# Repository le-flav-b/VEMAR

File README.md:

Technical Documentation: Project VEMAR
======================================
Vehicle for Exploration, Mapping & Air-quality Reconnaissance
-------------------------------------------------------------

**VEMAR** is a modular platform designed for environmetal monitoring and spatial mapping.
By combining real-time locomotion control with a verstile *plug-and-play* sensor architecture, VEMAR provides a comprehensive solution for atmospheric analysis in diverse environments.

## System Overview

The VEMAR system consists of three primary layers:
* A remote controlled vehicle
* Modular Sensors
* Remote Controller

The architecture is designed for high adaptability, allowing users to reconfigure the hardware loadout without complex software recalibration.

### Mobile Platform
* Locomotion: Multi-directional drive system.
* Storage: Integrated SD card slot for localized data logging (JSON format)
* Connectivity: Real-time telemetry link between the vehicle and the handheld controller.

### Modular Sensor Suite
The system utilizes a unified interface that allows the controller to automatically detect and initialize snensors upon connection.

| Sensor ID | Sensor Category | Parameters Measured                                         |
|:---------:|:---------------:|:-----------------------------------------------------------:|
| 1         | Atmospheric     | Temperature, Humidity, Barometric Pressure, PM2.5, PM10     |
| 2         | Gas Analysis    | O2, CO2, CO, NH3, NO2                                       |
| 3         | Mapping         | LiDAR (Light Detection and Ranging) for 2D spatial modeling |
| 4         | Radiation       | Ionizing radiation levels (Geiger-Müller detection)         |

## Functional Capabilities

### Remote Control

The end-user manages the vehicle's navigation via a dedicated controller.
The control link facilites:
* Manual Drive: Real-time steering.
* Data Visualization: A live feedback loop where sensor readings are streamed directly to the controller's display.

### Plug-and-Play Architecture

VEMAR eliminates the need for manual firmware updates when switching hardware.
* Auto-Detection: When a sensor module is attached, the controller identifies the hardware ID and adjusts the UI to display the relevant metrics.
* Hot-Swapping: Sensors can be exchanged in the field to pivot from air-quality monitoring to radiation detection or mapping.

### Data Management

The system supports dual-stream data handling:
* Live Monitoring: Immediate visaul feedback on the controller screen for rapid assessment.
* Archival Recording: On-demand recording to an onboard **SD Card**. this ensures high-fidelity data retention for post-mission analysis and mapping reconstruction.

> Caution: Removing the SD card before stopping the recording may result data corruption of the sd card.
It is recommended to wait at least 5 seconds after disabling saving before safely removing the SD card.

## Operation Workflow

1. Initialization: Power on the vehicle and controller.
2. Module Integration: Plug in desired sensor modules.
3. Verification: Cycle through sensor module readings by pressing the 'A' button on the controller.
4. Deployment: Navigate VEMAR into the target zone while monitoring live data.
5. Logging: Toggle the `Record` function to save data to the SD card by pressing 'B'.
6. Recovery: Disable data logging and retrieve the SD card for data processing.

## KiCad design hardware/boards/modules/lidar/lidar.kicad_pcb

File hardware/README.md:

explain the folder + show what can be found where

NEED TO CLEAN UP LIBS, some are not used, and architecture is strange
check component one by one and make agreement (e.g : there is 4pin_quartz in differents libs and the symbol don't even look the same)

and also COMPLETE SYMBOLS with datasheet, footprint, ...

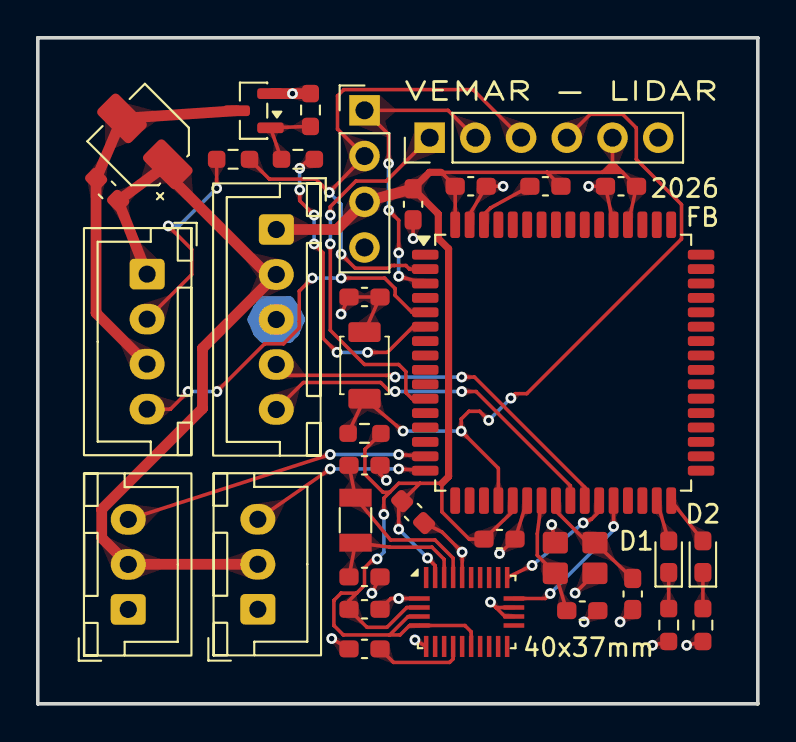
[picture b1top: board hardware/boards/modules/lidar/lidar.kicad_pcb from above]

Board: 2 copper layers, 40.0 x 37.0 mm, 35 parts (0 on the bottom side), 28 nets.

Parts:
C1, C5, C6, C7, C8, C10, C13, C14: 100nF; C_0603_1608Metric_Pad1.08x0.95mm_HandSolder
C2, C3, C11, C12: 12pF; C_0603_1608Metric_Pad1.08x0.95mm_HandSolder
C4: 4.7uF; C_0603_1608Metric_Pad1.08x0.95mm_HandSolder
C9: 10uF; CP_Elec_4x5.4
C15: 1uF; C_0603_1608Metric_Pad1.08x0.95mm_HandSolder
D1: GREEN; LED_0603_1608Metric_Pad1.05x0.95mm_HandSolder
D2: RED; LED_0603_1608Metric_Pad1.05x0.95mm_HandSolder
J1: JST; JST_XH_B5B-XH-A_1x05_P2.50mm_Vertical
J2: Dupont; PinHeader_1x06_P2.54mm_Vertical
J3: Dupont; PinHeader_1x04_P2.54mm_Vertical
J4: JST; JST_XH_B4B-XH-A_1x04_P2.50mm_Vertical
J5, J6: JST; JST_XH_B3B-XH-A_1x03_P2.50mm_Vertical
Q1: AO3400A; SOT-23
R1, R5: 10K; R_0603_1608Metric_Pad0.98x0.95mm_HandSolder
R2, R3: 330; R_0603_1608Metric_Pad0.98x0.95mm_HandSolder
R4: 100; R_0603_1608Metric_Pad0.98x0.95mm_HandSolder
R6: 1K; R_0603_1608Metric_Pad0.98x0.95mm_HandSolder
SW1: SW_Push; SW_Tactile3x2.5
U1: ATmega128A; TQFP-64_14x14mm_P0.8mm
U2: BNO055; BNO055_Hand_Soldering_LGA-28_5.2x3.8mm_P0.5mm
Y1: 16MHz; crys_osc_smd3225_4
Y2: 32.768kHz; Crystal_SMD_3215-2Pin_3.2x1.5mm

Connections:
3V3: C4.1, C5.1, C6.1, C7.1, C8.1, C13.2, C14.1, J1.1 (3V3), J2.5, J3.3, R1.1, U1.21 (VCC), U1.52 (VCC), U1.64 (AVCC), U2.3 (VDD), U2.4 (~BOOT_LOAD_PIN), U2.5 (PS1), U2.11 (~RESET), U2.28 (VDDIO)
5V: C9.1, C10.1, J1.2 (5V), J4.1, J5.2, J6.2
D1: D1.2 (A), U1.31 (PD6)
D2: D2.2 (A), U1.32 (PD7)
GND: C1.1, C1.2, C2.2, C3.2, C4.2, C5.2, C6.2, C7.2, C11.2, C12.2, C13.1, C14.2, C15.2, J1.3 (GND), J2.6, J3.4, J5.1, J6.1, Q1.2 (S), R2.2, R3.2, R5.1, SW1.1, U1.22 (GND), U1.53 (GND), U1.63 (GND), U2.2 (GND), U2.6 (PS0), U2.17 (COM3), U2.18 (COM2), U2.25 (GNDIO), Y1.2 (G), Y1.4 (G)
LIDAR_EN: R4.1, U1.6 (PE4)
LIDAR_PWM: J4.4, U1.5 (PE3)
unnamed: D1.1 (K), R2.1
unnamed: D2.1 (K), R3.1
unnamed: J4.2, R6.2
unnamed: C9.2, C10.2, J4.3, Q1.3 (D)
unnamed: Q1.1 (G), R4.2, R5.2
unnamed: C8.2, U1.62 (AREF)
unnamed: C2.1, U1.24 (XTAL1), Y1.1
unnamed: C3.1, U1.23 (XTAL2), Y1.3
unnamed: C15.1, U2.9 (CAP)
unnamed: C12.1, U2.27 (XIN32), Y2.1
unnamed: C11.1, U2.26 (XOUT32), Y2.2
RST: J2.4, R1.2, SW1.2, U1.20 (~RESET)
RX0: J2.3, J3.2, R6.1, U1.2 (PE0)
RX1: U1.27 (PD2), U2.20 (COM0)
SCK: J2.1, U1.11 (PB1)
SCL: J1.5 (SCL), U1.25 (PD0)
SDA: J1.4 (SDA), U1.26 (PD1)
SERVO_A_PWM: J5.3, U1.15 (PB5)
SERVO_B_PWM: J6.3, U1.16 (PB6)
TX0: J2.2, J3.1, U1.3 (PE1)
TX1: U1.28 (PD3), U2.19 (COM1)

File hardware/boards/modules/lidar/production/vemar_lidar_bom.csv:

Designator,Footprint,Quantity,Value,LCSC Part #
"C1, C10, C13, C14, C5, C6, C7, C8",0603,8,100nF,
"C11, C12, C2, C3",0603,4,12pF,
C15,0603,1,1uF,
C4,0603,1,4.7uF,
C9,CP_Elec_4x5.4,1,10uF,
D1,0603,1,GREEN,
D2,0603,1,RED,
J1,JST_XH_B5B-XH-A_1x05_P2.50mm_Vertical,1,JST,
J2,PinHeader_1x06_P2.54mm_Vertical,1,Dupont,
J3,PinHeader_1x04_P2.54mm_Vertical,1,Dupont,
J4,JST_XH_B4B-XH-A_1x04_P2.50mm_Vertical,1,JST,
"J5, J6",JST_XH_B3B-XH-A_1x03_P2.50mm_Vertical,2,JST,
Q1,SOT-23,1,AO3400A,
"R1, R5",0603,2,10K,
"R2, R3",0603,2,330,
R4,0603,1,100,
R6,0603,1,1K,
SW1,SW_Tactile3x2.5,1,SW_Push,
U1,TQFP-64_14x14mm_P0.8mm,1,ATmega128A,
U2,BNO055_Hand_Soldering_LGA-28_5.2x3.8mm_P0.5mm,1,BNO055,
Y1,crys_osc_smd3225_4,1,16MHz,
Y2,Crystal_SMD_3215-2Pin_3.2x1.5mm,1,32.768kHz,

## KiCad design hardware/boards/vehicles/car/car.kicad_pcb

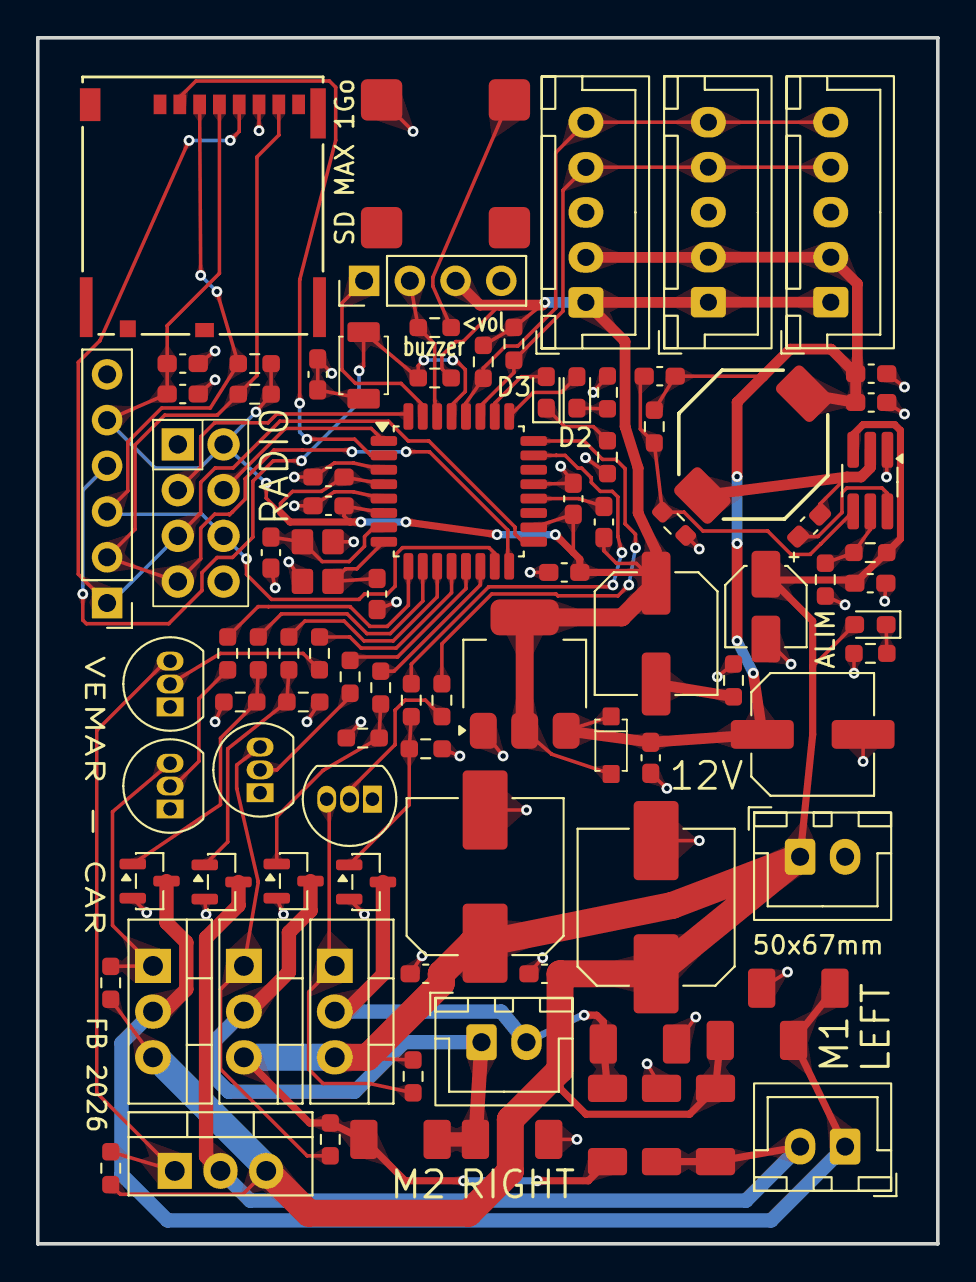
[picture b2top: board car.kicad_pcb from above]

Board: 2 copper layers, 50.0 x 67.0 mm, 94 parts (0 on the bottom side), 53 nets.

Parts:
BT1: JST; JST_XH_B2B-XH-A_1x02_P2.50mm_Vertical
BZ1: Buzzer; buzzer_8.5x8.5
C1, C5, C6, C7, C8, C10, C11, C16, C18, C21, C23: 100nF; C_0603_1608Metric_Pad1.08x0.95mm_HandSolder
C2, C3: 12pF; C_0603_1608Metric_Pad1.08x0.95mm_HandSolder
C4: 4.7uF; C_0603_1608Metric_Pad1.08x0.95mm_HandSolder
C9: 10uF; CP_Elec_4x5.4
C12, C13: 22uF; C_0603_1608Metric_Pad1.08x0.95mm_HandSolder
C14: 75pF; C_0603_1608Metric_Pad1.08x0.95mm_HandSolder
C15, C17: 22uF; CP_Elec_6.3x5.4
C19: 10uF; C_0603_1608Metric_Pad1.08x0.95mm_HandSolder
C20, C22: 470uF; CP_Elec_8x10.5
D1, D3: RED; LED_0603_1608Metric_Pad1.05x0.95mm_HandSolder
D2: GREEN; LED_0603_1608Metric_Pad1.05x0.95mm_HandSolder
D4: RS1MFA; D_SOD123
D5, D6, D7, D8, D9, D10, D11, D12: SS36; SMA(DO-214AC)
J1: Dupont; PinHeader_1x06_P2.54mm_Vertical
J2: Dupont; PinHeader_1x04_P2.54mm_Vertical
J3: Dupont; Pin_02x04
J4, J5, J6: JST; JST_XH_B5B-XH-A_1x05_P2.50mm_Vertical
L1: 10uH; Inductor_octogone
M1: LEFT; JST_XH_B2B-XH-A_1x02_P2.50mm_Vertical
M2: RIGHT; JST_XH_B2B-XH-A_1x02_P2.50mm_Vertical
Q1, Q2, Q7, Q8: FQP27P06; TO-220-3_Vertical
Q3, Q4, Q9, Q10: AO3400A; SOT-23
Q5, Q6, Q11, Q12: 2N3904; TO-92_Inline
R1: 680; R_0603_1608Metric_Pad0.98x0.95mm_HandSolder
R2, R13, R14, R21, R22, R29, R30: 10K; R_0603_1608Metric_Pad0.98x0.95mm_HandSolder
R3, R4: 330; R_0603_1608Metric_Pad0.98x0.95mm_HandSolder
R5: ?; R_0603_1608Metric_Pad0.98x0.95mm_HandSolder
R6, R7, R19, R20, R27, R28: 4.7K; R_0603_1608Metric_Pad0.98x0.95mm_HandSolder
R8: 511K; R_0603_1608Metric_Pad0.98x0.95mm_HandSolder
R9: 105K; R_0603_1608Metric_Pad0.98x0.95mm_HandSolder
R10: 43.2K; R_0603_1608Metric_Pad0.98x0.95mm_HandSolder
R11: 5.76K; R_0603_1608Metric_Pad0.98x0.95mm_HandSolder
R12: 1; R_0603_1608Metric_Pad0.98x0.95mm_HandSolder
R15, R16, R23, R24: 1K; R_0603_1608Metric_Pad0.98x0.95mm_HandSolder
R17, R18, R25, R26: 47; R_0603_1608Metric_Pad0.98x0.95mm_HandSolder
SD1: SD Card Slot; SD_SLOT
SW1: SW_Push; SW_Tactile3x2.5
U1: ATmega328P-A; TQFP-32_7x7mm_P0.8mm
U2: TPS54302; TSOT-23-6_HandSoldering
U3: AMS1117-3.3; SOT-223-3_TabPin2
Y1: 16MHz; crys_osc_smd3225_4

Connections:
3V3: C4.1, C5.1, C6.1, C7.1, C8.1, C17.1, C18.1, C19.1, D4.2 (A), J1.5, J2.3, J3.8, J4.1, J5.1, J6.1, R2.1, R6.1, R7.1, R13.1, R14.1, SD1.4 (VDD), U1.4 (VCC), U1.6 (VCC), U1.18 (AVCC), U3.2 (VO)
5V: C12.1, C13.2, C14.2, C15.1, C16.2, D4.1 (K), J4.2, J5.2, J6.2, L1.2, R10.2, U3.3 (VI)
12V: BT1.1 (+), C9.1, C10.2, C20.1, C21.1, C22.1, C23.1, D1.2 (A), D5.1 (K), D7.1 (K), D9.1 (K), D11.1 (K), Q1.3 (S), Q2.3 (S), Q7.3 (S), Q8.3 (S), R8.2, R19.2, R20.1, R27.2, R28.1, U2.3 (VIN)
D2: D2.2 (A), U1.25 (PC2)
D3: D3.2 (A), U1.26 (PC3)
GND: BT1.2 (-), BZ1.2, C1.1, C1.2, C2.2, C3.2, C4.2, C5.2, C6.2, C7.2, C9.2, C10.1, C12.2, C13.1, C15.2, C16.1, C18.2, C19.2, C20.2, C21.2, C22.2, C23.2, D6.2 (A), D8.2 (A), D10.2 (A), D12.2 (A), J1.6, J2.4, J3.1, J4.3, J5.3, J6.3, Q3.2 (S), Q4.2 (S), Q5.1 (E), Q6.1 (E), Q9.2 (S), Q10.2 (S), Q11.1 (E), Q12.1 (E), R1.2, R3.2, R4.2, R9.1, R11.1, R12.1, R21.2, R22.1, R29.2, R30.1, SD1.6 (VSS), SW1.1, U1.3 (GND), U1.5 (GND), U1.21 (GND), U2.1 (GND), U3.1 (GND), Y1.2 (G), Y1.4 (G)
M1_EN_CCW: R16.1, U1.12 (PB0)
M1_EN_CW: R18.2, U1.11 (PD7)
M1_PWM_CCW: R17.2, U1.10 (PD6)
M1_PWM_CW: R15.1, U1.9 (PD5)
M2_EN_CCW: R24.1, U1.24 (PC1)
M2_EN_CW: R26.2, U1.23 (PC0)
M2_PWM_CCW: R25.2, U1.14 (PB2)
M2_PWM_CW: R23.1, U1.13 (PB1)
MISO: J1.2, J3.4, R14.2, SD1.7 (DAT0), U1.16 (PB4)
MOSI: J1.3, J3.6, R13.2, SD1.3 (CMD), U1.15 (PB3)
unnamed: BZ1.1, R5.2
unnamed: C17.2, R12.2
unnamed: D1.1 (K), R1.1
unnamed: D2.1 (K), R3.1
unnamed: D3.1 (K), R4.1
unnamed: D5.2 (A), D6.1 (K), M1.1 (+), Q1.2 (D), Q3.3 (D)
unnamed: D7.2 (A), D8.1 (K), M1.2 (-), Q2.2 (D), Q4.3 (D)
unnamed: D9.2 (A), D10.1 (K), M2.1 (+), Q7.2 (D), Q9.3 (D)
unnamed: D11.2 (A), D12.1 (K), M2.2 (-), Q8.2 (D), Q10.3 (D)
unnamed: Q1.1 (G), Q5.3 (C), R19.1
unnamed: Q2.1 (G), Q6.3 (C), R20.2
unnamed: Q3.1 (G), R17.1, R21.1
unnamed: Q4.1 (G), R18.1, R22.2
unnamed: Q5.2 (B), R15.2
unnamed: Q6.2 (B), R16.2
unnamed: Q9.1 (G), R25.1, R29.1
unnamed: Q10.1 (G), R26.1, R30.2
unnamed: Q11.2 (B), R23.2
unnamed: Q7.1 (G), Q11.3 (C), R27.1
unnamed: Q12.2 (B), R24.2
unnamed: Q8.1 (G), Q12.3 (C), R28.2
unnamed: C8.2, U1.20 (AREF)
unnamed: C2.1, U1.7 (XTAL1/PB6), Y1.1
unnamed: C3.1, U1.8 (XTAL2/PB7), Y1.3
unnamed: C11.1, U2.6 (BOOT)
unnamed: R8.1, R9.2, U2.5 (EN)
unnamed: C14.1, R10.1, R11.2, U2.4 (FB)
unnamed: C11.2, L1.1, U2.2 (SW)
RC_CS: J3.7, U1.1 (PD3)
RC_EN: J3.2, U1.32 (PD2)
RST: J1.4, R2.2, SW1.2, U1.29 (~RESET/PC6)
RX: J2.2, R5.1, U1.30 (PD0)
SCK: J1.1, J3.3, SD1.5 (CLK), U1.17 (PB5)
SCL: J4.5, J5.5, J6.5, R7.2, U1.28 (PC5)
SDA: J4.4, J5.4, J6.4, R6.2, U1.27 (PC4)
SD_CS: SD1.2 (CD/DAT3), U1.2 (PD4)
TX: J2.1, U1.31 (PD1)

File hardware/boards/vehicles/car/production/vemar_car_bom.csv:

Designator,Footprint,Quantity,Value,LCSC Part #
BT1,JST_XH_B2B-XH-A_1x02_P2.50mm_Vertical,1,JST,
BZ1,buzzer_8.5x8.5,1,Buzzer,
"C1, C10, C11, C16, C18, C21, C23, C5, C6, C7, C8",0603,11,100nF,
"C12, C13",0603,2,22uF,
C14,0603,1,75pF,
"C15, C17",CP_Elec_6.3x5.4,2,22uF,
C19,0603,1,10uF,
"C2, C3",0603,2,12pF,
"C20, C22",CP_Elec_8x10.5,2,470uF,
C4,0603,1,4.7uF,
C9,CP_Elec_4x5.4,1,10uF,
"D1, D3",0603,2,RED,
"D10, D11, D12, D5, D6, D7, D8, D9",SMA(DO-214AC),8,SS36,
D2,0603,1,GREEN,
D4,D_SOD123,1,RS1MFA,
J1,PinHeader_1x06_P2.54mm_Vertical,1,Dupont,
J2,PinHeader_1x04_P2.54mm_Vertical,1,Dupont,
J3,Pin_02x04,1,Dupont,
"J4, J5, J6",JST_XH_B5B-XH-A_1x05_P2.50mm_Vertical,3,JST,
L1,Inductor_octogone,1,10uH,
M1,JST_XH_B2B-XH-A_1x02_P2.50mm_Vertical,1,LEFT,
M2,JST_XH_B2B-XH-A_1x02_P2.50mm_Vertical,1,RIGHT,
"Q1, Q2, Q7, Q8",TO-220-3_Vertical,4,FQP27P06,
"Q10, Q3, Q4, Q9",SOT-23,4,AO3400A,
"Q11, Q12, Q5, Q6",TO-92_Inline,4,2N3904,
R1,0603,1,680,
R10,0603,1,43.2K,
R11,0603,1,5.76K,
R12,0603,1,1,
"R13, R14, R2, R21, R22, R29, R30",0603,7,10K,
"R15, R16, R23, R24",0603,4,1K,
"R17, R18, R25, R26",0603,4,47,
"R19, R20, R27, R28, R6, R7",0603,6,4.7K,
"R3, R4",0603,2,330,
R5,0603,1,?,
R8,0603,1,511K,
R9,0603,1,105K,
SD1,SD_SLOT,1,SD Card Slot,
SW1,SW_Tactile3x2.5,1,SW_Push,
U1,TQFP-32_7x7mm_P0.8mm,1,ATmega328P-A,
U2,TSOT-23-6_HandSoldering,1,TPS54302,
U3,SOT-223-3_TabPin2,1,AMS1117-3.3,
Y1,crys_osc_smd3225_4,1,16MHz,

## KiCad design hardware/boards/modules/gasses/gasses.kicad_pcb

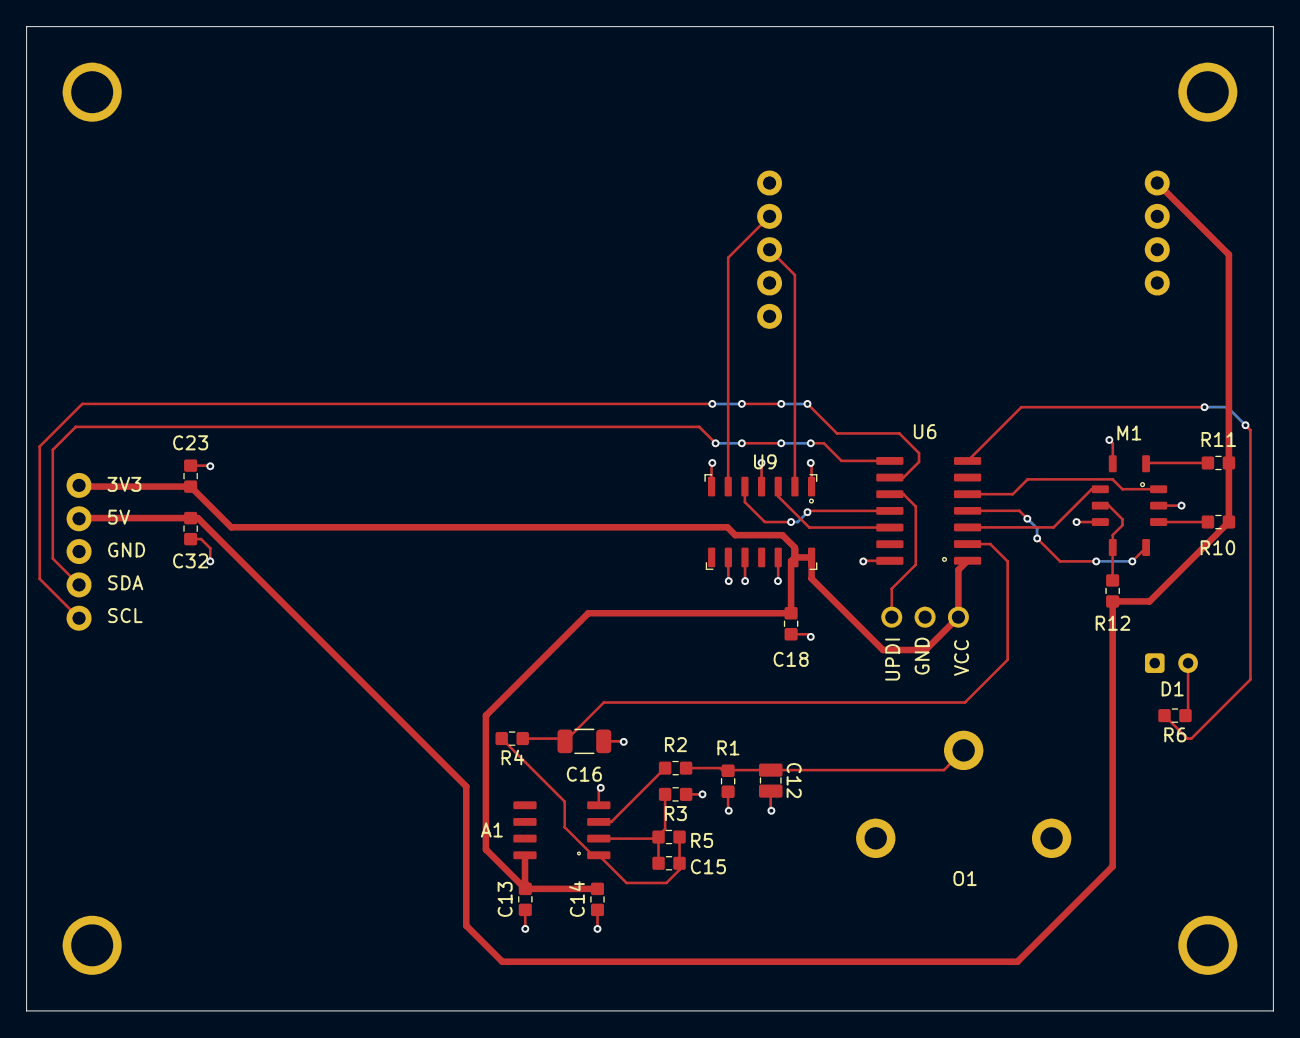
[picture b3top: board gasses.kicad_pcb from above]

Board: 2 copper layers, 95.0 x 75.0 mm, 26 parts (0 on the bottom side), 23 nets.

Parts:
A1: AD8552
C12: 4.7uF; C_0805
C13, C14, C15: 10nF; C_0603
C16: 10uF; C_1206
C18, C23, C32: 100nF; C_0603
D1: LED_3mm_THT
G2: Module Connector; GPIO_HEADER
J1: Program Header; ATtiny_Programming_Header
M1: MiCS-6814
O1: AO-03; AO_03
R1, R4: 100R; R_0603
R2, R3: 10K; R_0603
R5: 400K; R_0603
R6: 220; R_0603
R10: 27R; R_0603
R11: 130; R_0603
R12: 820R; R_0603
S5: MH-Z1911A
U6: ATtiny1614
U9: Buffer; SN74LVC125

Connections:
02_A: C16.2, R4.1, U6.2 (PA4)
3V3: A1.8 (+Vs), C13.2, C14.2, C18.1, C23.2, G2.1 (3V3), J1.1 (VCC), U6.1 (VDD), U9.13 (4OE), U9.14 (VCC)
5V: C32.1, G2.2 (5V), R10.2, R11.2, R12.1, S5.9 (VIN)
AT_GAS_RX: U6.12 (PA2), U9.3 (1Y)
AT_GAS_TX: U6.11 (PA1), U9.5 (2A)
CO2_RX: S5.4 (RX), U9.6 (2Y)
CO2_TX: S5.3 (TX), U9.2 (1A)
CO_VAL: M1.8 (H), U6.3 (PA5)
GND: A1.4 (-Vs), C12.2, C13.1, C14.1, C16.1, C18.2, C23.1, C32.2, D1.1 (K), G2.3 (GND), J1.2 (GND), M1.2 (B), M1.6 (F), M1.9 (J), O1.2 (Vsensor-), R1.1, R3.1, S5.8 (GND), U6.14 (GND), U9.1 (1OE), U9.4 (2OE), U9.7 (GND), U9.9 (3A), U9.10 (3OE), U9.12 (4A)
NH3_VAL: M1.4 (D), U6.4 (PA6)
NO2_VAL: M1.1 (A), U6.5 (PA7)
unnamed: A1.3 (+IN_A), R2.2
unnamed: A1.2 (-IN_A), C15.2, R3.2, R5.2
unnamed: A1.1 (OUT_A), C15.1, R4.2, R5.1
unnamed: D1.2 (A), R6.2
unnamed: M1.3 (C), R10.1
unnamed: M1.5 (E), M1.7 (G), R12.2
unnamed: M1.10 (K), R11.1
unnamed: C12.1, O1.1 (Vsensor+), R1.2, R2.1
SCL: G2.5 (SCL), U6.9 (PB0)
SDA: G2.4 (SDA), U6.8 (PB1)
STATUS_LED: R6.1, U6.7 (TOSC2/PB2)
UPDI: J1.3 (UPDI), U6.10 (PA0/RST/UPDI)

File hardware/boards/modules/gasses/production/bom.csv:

Designator,Footprint,Quantity,Value,LCSC Part #
"_4, _2",,2,,
"_3, ",mounting_hole,2,mounting_hole,
A1,AD8552,1,AD8552,
C12,C_0805,1,4.7uF,
"C13, C14, C15",C_0603,3,10nF,
C16,C_1206,1,10uF,
"C18, C23, C32",C_0603,3,100nF,
D1,LED_3mm_THT,1,~,
G2,GPIO_HEADER,1,Module Connector,
J1,ATtiny_Programming_Header,1,Program Header,
M1,MiCS-6814,1,MiCS-6814,
O1,AO_03,1,AO-03,
"R1, R4",R_0603,2,100R,
R10,R_0603,1,27R,
R11,R_0603,1,130,
R12,R_0603,1,820R,
"R2, R3",R_0603,2,10K,
R5,R_0603,1,400K,
R6,R_0603,1,220,
S5,MH-Z1911A,1,MH-Z1911A,
U6,ATtiny1614,1,~,
U9,SN74LVC125,1,Buffer,

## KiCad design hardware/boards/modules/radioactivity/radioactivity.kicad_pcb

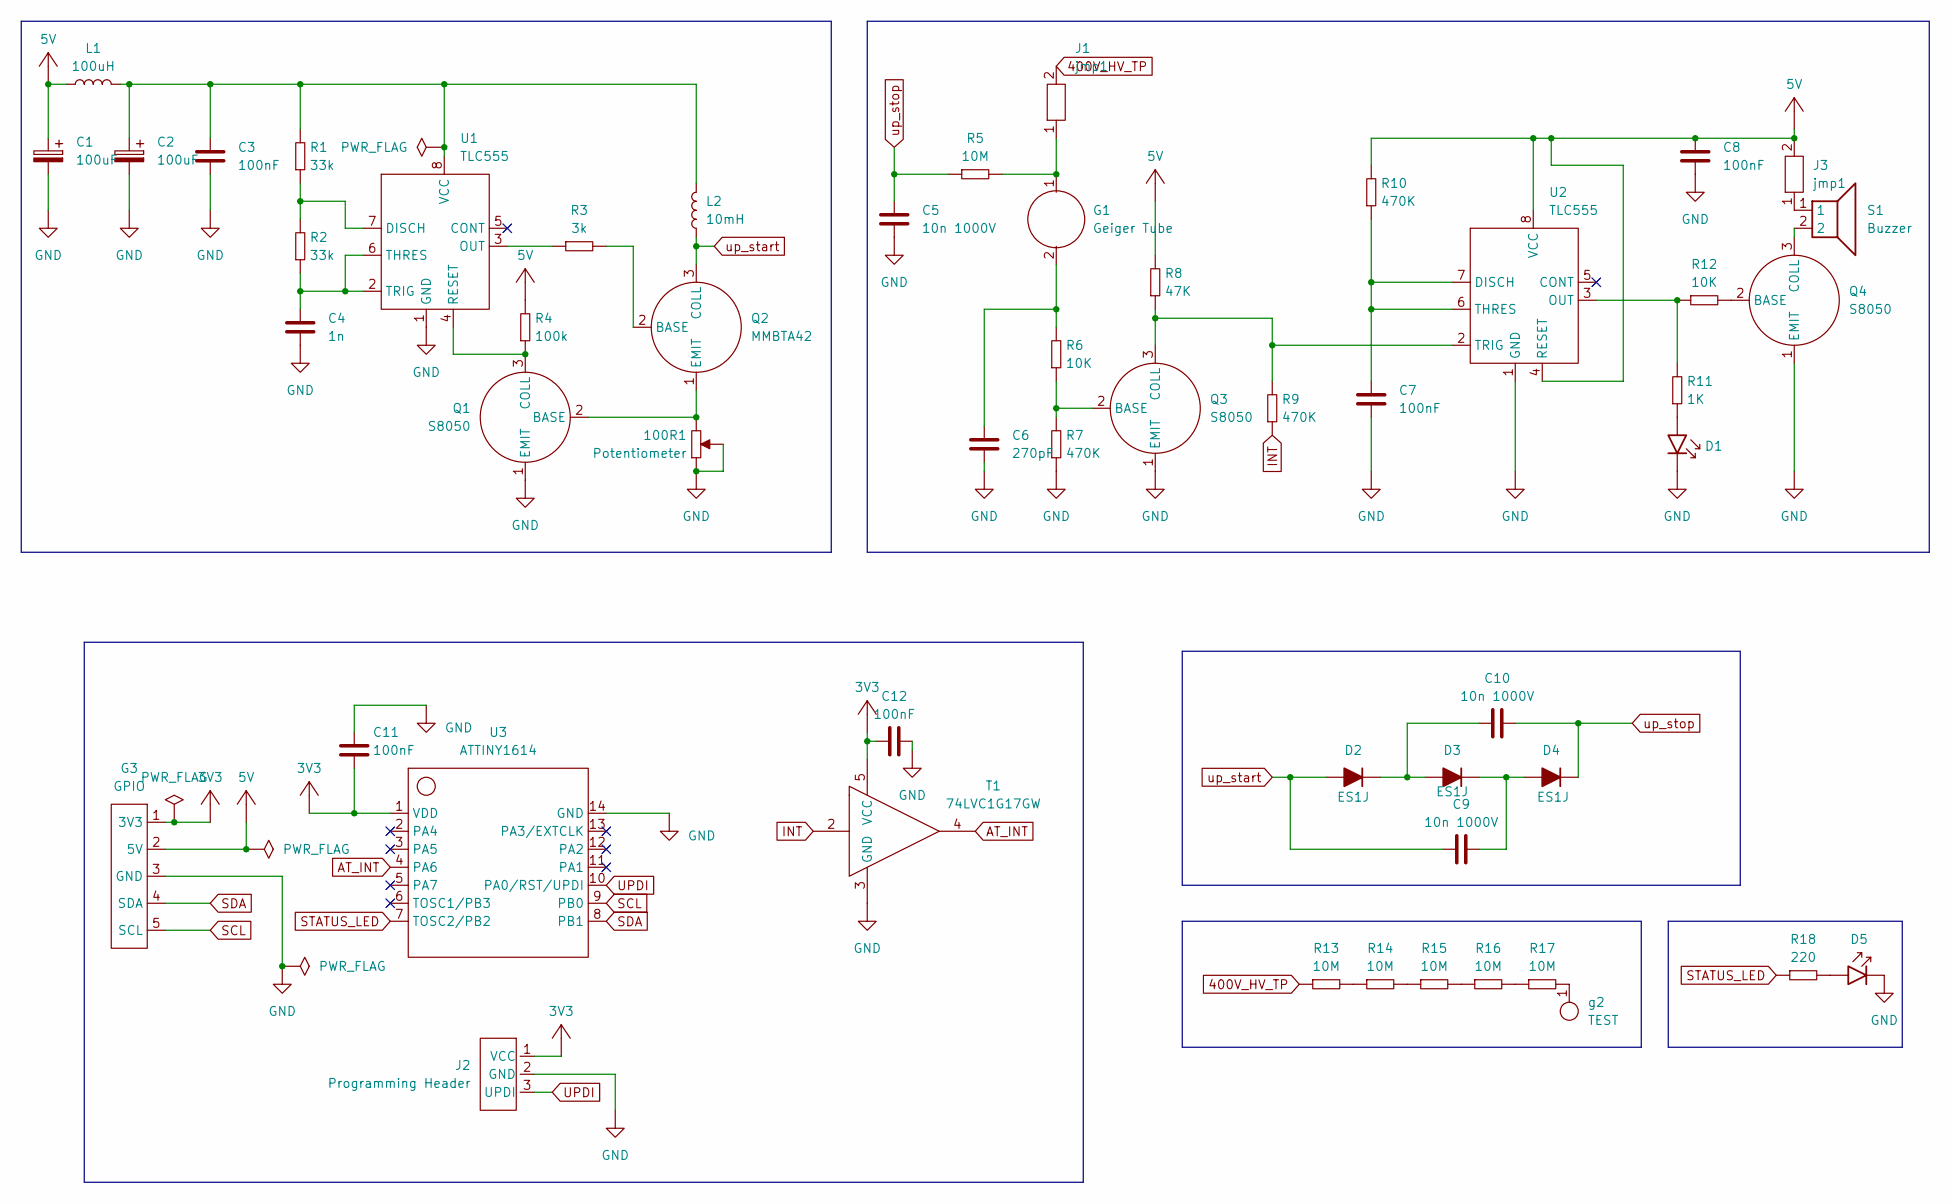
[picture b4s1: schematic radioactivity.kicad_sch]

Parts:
100R1: Potentiometer; SMD_3P_3.8X3.6
C1, C2: 100uF; C_Elec_SMD_5x5.4
C3, C7, C8, C11, C12: 100nF; C_0603
C4: 1n; C_0603
C5, C9, C10: 10n 1000V; C_1206
C6: 270pF; C_0603
D1: LED_0603
D2, D3, D4: ES1J; SMA(DO-214AC)
D5: LED_3mm_THT
G1: Geiger Tube; Geiger_Tube_J305
G3: GPIO; GPIO_HEADER
J1, J3: jmp1; Jumper_2
J2: Programming Header; ATtiny_Programming_Header
L1: 100uH; SMD(7.1x6.6)
L2: 10mH; C_0603
Q1, Q3, Q4: S8050; SOT-23
Q2: MMBTA42; SOT-23
R1, R2: 33k; R_0603
R3: 3k; R_0603
R4: 100k; R_0603
R5, R13, R14, R15, R16, R17: 10M; R_0603
R6, R12: 10K; R_0603
R7, R9, R10: 470K; R_0603
R8: 47K; R_0603
R11: 1K; R_0603
R18: 220; R_0603
S1: Buzzer; buzzer_8.5x8.5
T1: 74LVC1G17GW; SOT353
U1, U2: TLC555; SOIC-8
U3: ATTINY1614; ATtiny1614
g2: TEST; gpio_1

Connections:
400V_HV_TP: J1.2, R13.1
AT_INT: T1.4, U3.4 (PA6)
INT: R9.1, T1.2
unnamed: C6.2, G1.2, R6.2
unnamed: D1.2 (A), R11.1
unnamed: C10.1, D2.1 (K), D3.2 (A)
unnamed: C9.2, D3.1 (K), D4.2 (A)
unnamed: D5.2 (A), R18.2
unnamed: G1.1, J1.1, R5.2
unnamed: J3.1, S1.1
unnamed: 100R1.3, Q1.2 (BASE), Q2.1 (EMIT)
unnamed: Q1.3 (COLL), R4.1, U1.4 (RESET)
unnamed: Q2.2 (BASE), R3.2
unnamed: Q3.2 (BASE), R6.1, R7.2
unnamed: Q3.3 (COLL), R8.1, R9.2, U2.2 (TRIG)
unnamed: Q4.2 (BASE), R12.2
unnamed: Q4.3 (COLL), S1.2
unnamed: R13.2, R14.1
unnamed: R14.2, R15.1
unnamed: R15.2, R16.1
unnamed: R16.2, R17.1
unnamed: R17.2, g2.1
unnamed: R1.1, R2.2, U1.7 (DISCH)
unnamed: R3.1, U1.3 (OUT)
unnamed: C4.2, R2.1, U1.2 (TRIG), U1.6 (THRES)
unnamed: C7.2, R10.1, U2.6 (THRES), U2.7 (DISCH)
unnamed: R11.2, R12.1, U2.3 (OUT)
SCL: G3.5 (SCL), U3.9 (PB0)
SDA: G3.4 (SDA), U3.8 (PB1)
STATUS_LED: R18.1, U3.7 (TOSC2/PB2)
UPDI: J2.3 (UPDI), U3.10 (PA0/RST/UPDI)
up_start: C9.1, D2.2 (A), L2.1, Q2.3 (COLL)
up_stop: C5.2, C10.2, D4.1 (K), R5.1

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
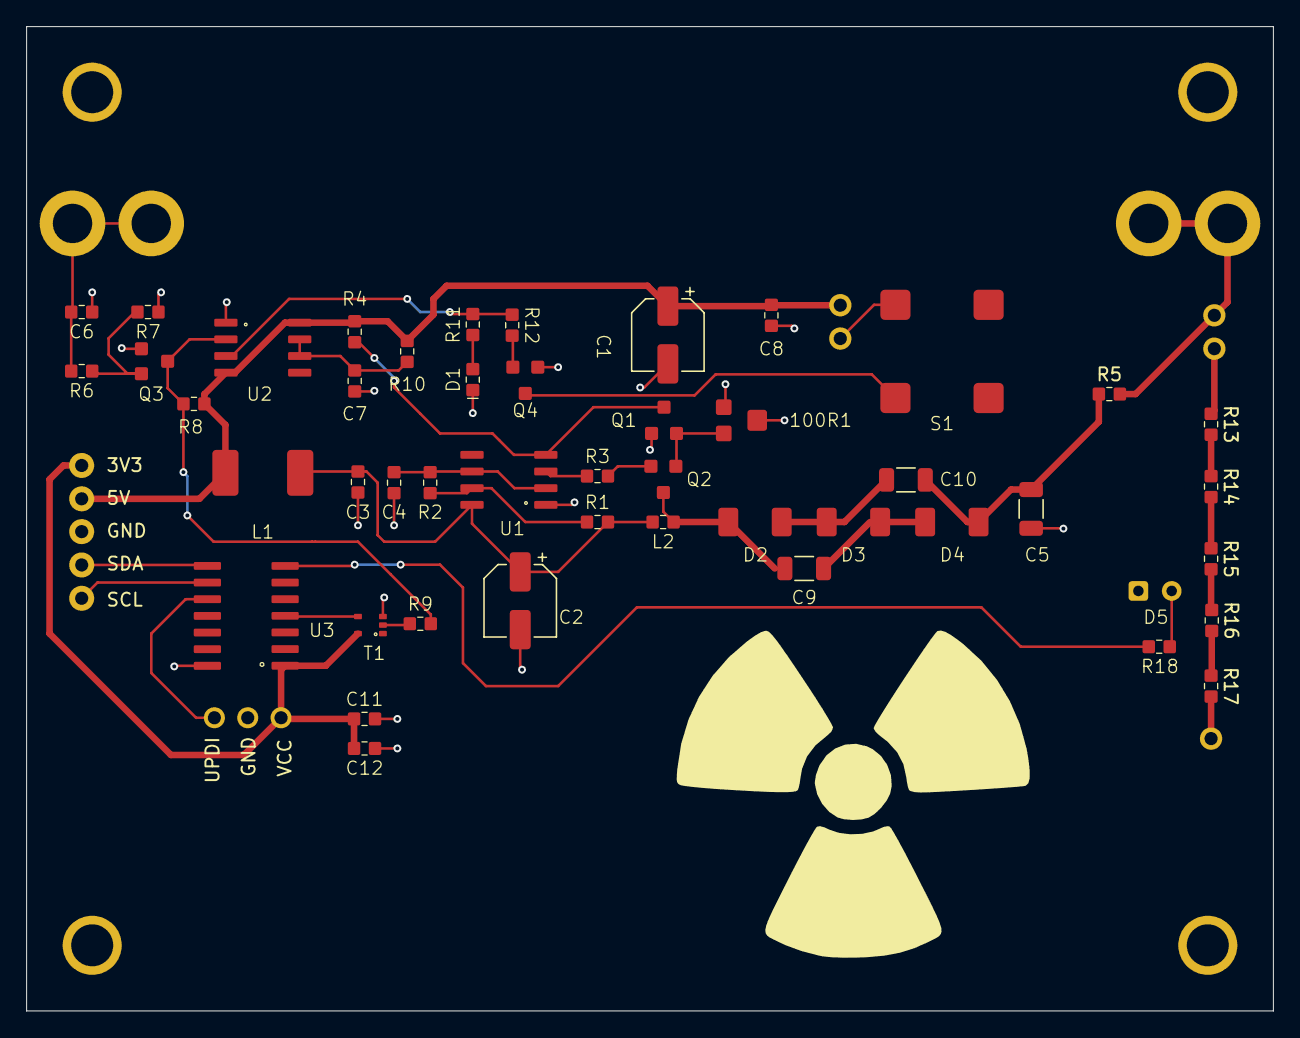
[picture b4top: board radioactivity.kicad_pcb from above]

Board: 2 copper layers, 95.0 x 75.0 mm, 53 parts (0 on the bottom side), 37 nets.

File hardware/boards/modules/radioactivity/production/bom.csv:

Designator,Footprint,Quantity,Value,LCSC Part #
"_3, _2, ",,3,,
100R1,SMD_3P_3.8X3.6,1,Potentiometer,
"C10, C5, C9",C_1206,3,10n 1000V,
C12,C_0603,1,100nF,
C6,C_0603,1,270pF,
"D2, D3, D4",SMA(DO-214AC),3,ES1J,
D5,LED_3mm_THT,1,~,
G2,gpio_1,1,TEST,
J3,Jumper_2,1,jmp1,
L1,SMD(7.1x6.6),1,100uH,
L2,C_0603,1,10mH,
"Q1, Q3, Q4",SOT-23,3,S8050,
Q2,SOT-23,1,MMBTA42,
"R1, R2",R_0603,2,33k,
"R10, R7, R9",R_0603,3,470K,
"R12, R6",R_0603,2,10K,
"R13, R14, R15, R16, R17, R5",R_0603,6,10M,
R18,R_0603,1,220,
R3,R_0603,1,3k,
R4,R_0603,1,100k,
R8,R_0603,1,47K,
S1,buzzer_8.5x8.5,1,Speaker,
T1,SOT353,1,74LVC1G17GW,
"U1, U2",SOIC-8,2,TLC555,
U3,ATtiny1614,1,ATTINY1614,

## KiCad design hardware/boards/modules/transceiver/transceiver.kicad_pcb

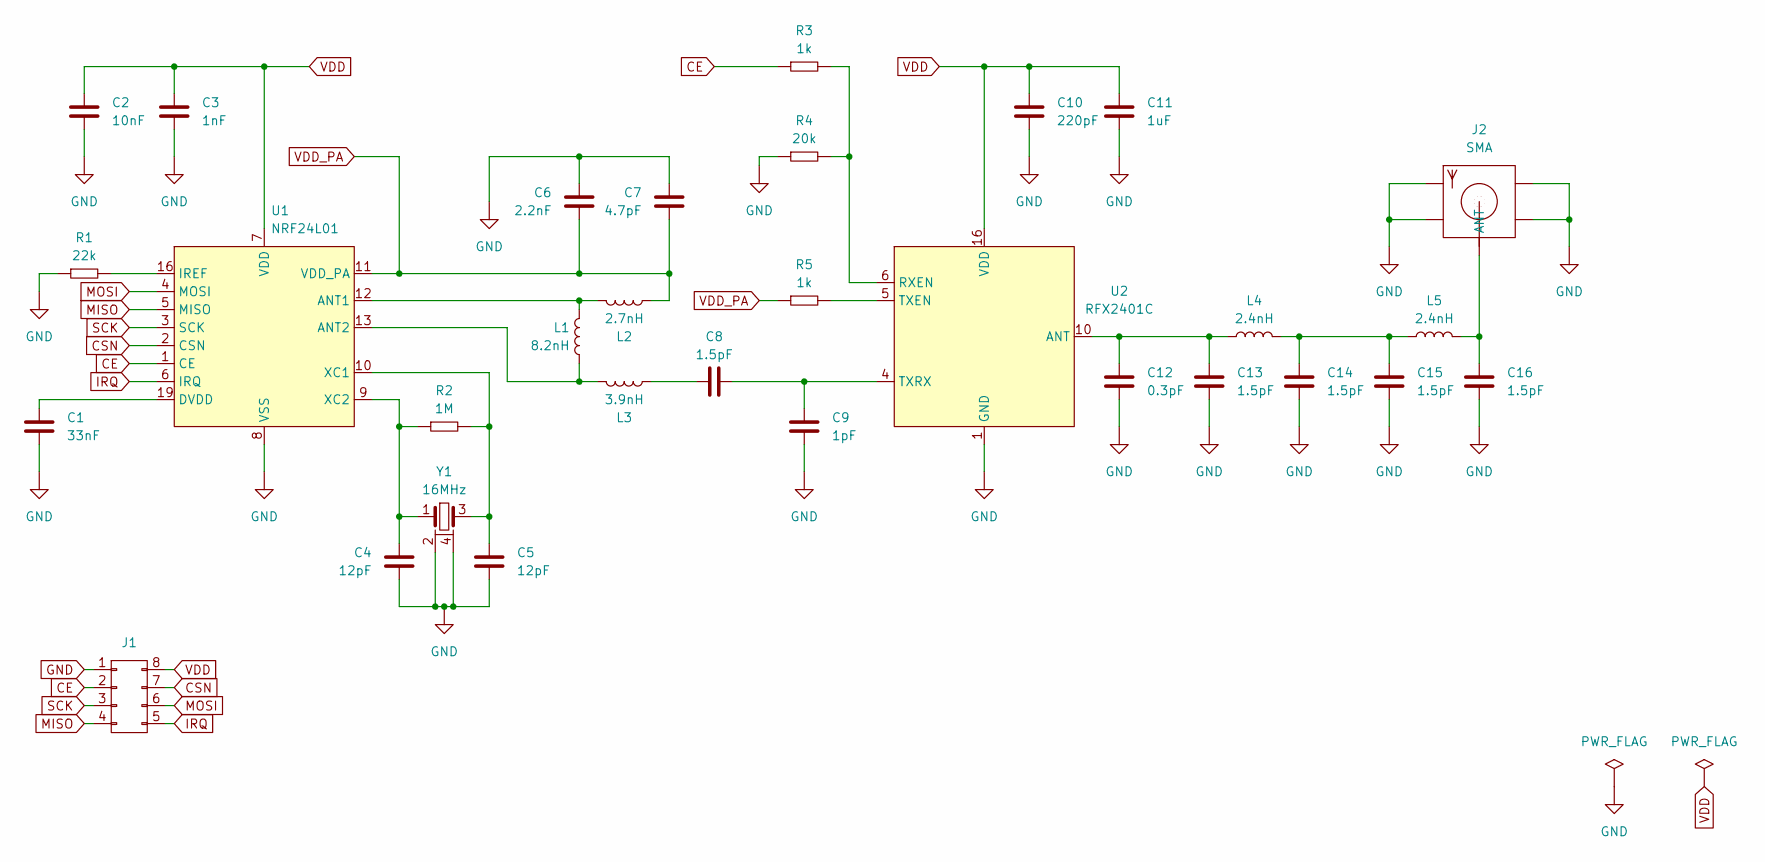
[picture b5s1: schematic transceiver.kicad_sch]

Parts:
C1: 33nF; C_0402; Mfr. Part 0402B333K160CT; LCSC C301939
C2: 10nF; C_0402; Mfr. Part CC0402KRX7R9BB103; LCSC C60133
C3: 1nF; C_0402; Mfr. Part CL05B102KB5NNNC; LCSC C14442
C4, C5: 12pF; C_0402; Mfr. Part CC0402GRNPO9BN120; LCSC C526985
C6: 2.2nF; C_0402; Mfr. Part CC0402KRX7R9BB222; LCSC C106861
C7: 4.7pF; C_0402; Mfr. Part CC0402CRNPO9BN4R7; LCSC C189469
C8, C13, C14, C15, C16: 1.5pF; C_0402; Mfr. Part 0402CG1R5C500NT; LCSC C1552
C9: 1pF; C_0402; Mfr. Part CC0402BRNPO9BN1R0; LCSC C309455
C10: 220pF; C_0402; Mfr. Part CC0402JRNPO9BN221; LCSC C107001
C11: 1uF; C_0402; Mfr. Part CL05B105KQ5NQNC; LCSC C307427
C12: 0.3pF; C_0402; Mfr. Part 0402CG0R3B500NT; LCSC C880415
J1: Pin_02x04
J2: SMA
L1: 8.2nH; L_0402; Mfr. Part LQW15AN8N2G80D; LCSC C307610
L2: 2.7nH; L_0402; Mfr. Part LQW15AN2N7G80D; LCSC C412269
L3: 3.9nH; L_0402; Mfr. Part LQW15AN3N9G80D; LCSC C412279
L4, L5: 2.4nH; L_0402; Mfr. Part LQW15AN2N4B00D; LCSC C113113
R1: 22k; R_0402; Mfr. Part FRC0402F2202TS; LCSC C2909337
R2: 1M; R_0402; Mfr. Part 0402WGF1004TCE; LCSC C26083
R3, R5: 1k; R_0402; Mfr. Part FRC0402F1001TS; LCSC C2906864
R4: 20k; R_0402; Mfr. Part FRC0402F2002TS; LCSC C2906867
U1: NRF24L01; NRF24L01_QFN20; Mfr. Part NRF24L01P-R; LCSC C8791
U2: RFX2401C; RFX2401C_QFN16; Mfr. Part RFX2401C; LCSC C19213
Y1: 16MHz; Crystal_3225; Mfr. Part X322516MLB4SI; LCSC C13738

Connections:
CE: J1.2, R3.1, U1.1 (CE)
CSN: J1.7, U1.2 (CSN)
IRQ: J1.5, U1.6 (IRQ)
MISO: J1.4, U1.5 (MISO)
MOSI: J1.6, U1.4 (MOSI)
unnamed: C8.2, L3.2
unnamed: C14.2, C15.2, L4.2, L5.1
unnamed: C16.2, J2.1 (ANT), L5.2
unnamed: L1.1, L2.1, U1.12 (ANT1)
unnamed: L1.2, L3.1, U1.13 (ANT2)
unnamed: C1.2, U1.19 (DVDD)
unnamed: R1.2, U1.16 (IREF)
unnamed: C5.2, R2.2, U1.10 (XC1), Y1.3
unnamed: C4.2, R2.1, U1.9 (XC2), Y1.1
unnamed: C12.2, C13.2, L4.1, U2.10 (ANT)
unnamed: R3.2, R4.2, U2.6 (RXEN)
unnamed: R5.2, U2.5 (TXEN)
unnamed: C8.1, C9.2, U2.4 (TXRX)
SCK: J1.3, U1.3 (SCK)
VDD_PA: C6.1, C7.2, L2.2, R5.1, U1.11 (VDD_PA)

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
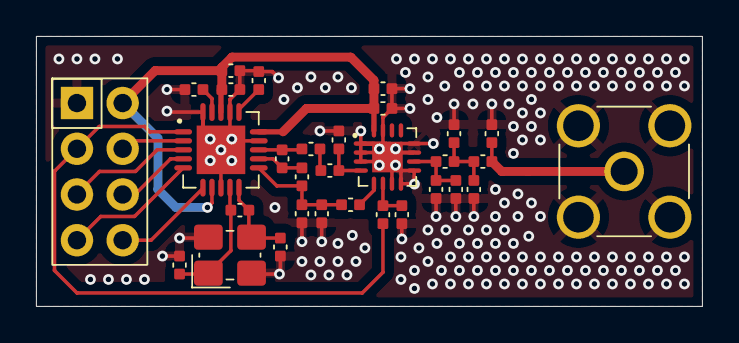
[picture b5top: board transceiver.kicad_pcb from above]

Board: 2 copper layers, 37.0 x 15.0 mm, 31 parts (0 on the bottom side), 22 nets.

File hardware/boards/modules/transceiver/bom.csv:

"Reference","Qty","Value","Footprint","Mfr. Part","LCSC"
"J1","1","~","connector:Pin_02x04","",""
"J2","1","SMA","connector:SMA","",""
"C8,C13,C14,C15,C16","5","1.5pF","common:C_0402","0402CG1R5C500NT","C1552"
"U1","1","NRF24L01","transceiver:NRF24L01_QFN20","NRF24L01P-R","C8791"
"Y1","1","16MHz","common:Crystal_3225","X322516MLB4SI","C13738"
"C3","1","1nF","common:C_0402","CL05B102KB5NNNC","C14442"
"U2","1","RFX2401C","transceiver:RFX2401C_QFN16","RFX2401C","C19213"
"R2","1","1M","common:R_0402","0402WGF1004TCE","C26083"
"C2","1","10nF","common:C_0402","CC0402KRX7R9BB103","C60133"
"C6","1","2.2nF","common:C_0402","CC0402KRX7R9BB222","C106861"
"C10","1","220pF","common:C_0402","CC0402JRNPO9BN221","C107001"
"L4,L5","2","2.4nH","common:L_0402","LQW15AN2N4B00D","C113113"
"C7","1","4.7pF","common:C_0402","CC0402CRNPO9BN4R7","C189469"
"C1","1","33nF","common:C_0402","0402B333K160CT","C301939"
"C11","1","1uF","common:C_0402","CL05B105KQ5NQNC","C307427"
"L1","1","8.2nH","common:L_0402","LQW15AN8N2G80D","C307610"
"C9","1","1pF","common:C_0402","CC0402BRNPO9BN1R0","C309455"
"L2","1","2.7nH","common:L_0402","LQW15AN2N7G80D","C412269"
"L3","1","3.9nH","common:L_0402","LQW15AN3N9G80D","C412279"
"C4,C5","2","12pF","common:C_0402","CC0402GRNPO9BN120","C526985"
"C12","1","0.3pF","common:C_0402","0402CG0R3B500NT","C880415"
"R3,R5","2","1k","common:R_0402","FRC0402F1001TS","C2906864"
"R4","1","20k","common:R_0402","FRC0402F2002TS","C2906867"
"R1","1","22k","common:R_0402","FRC0402F2202TS","C2909337"
